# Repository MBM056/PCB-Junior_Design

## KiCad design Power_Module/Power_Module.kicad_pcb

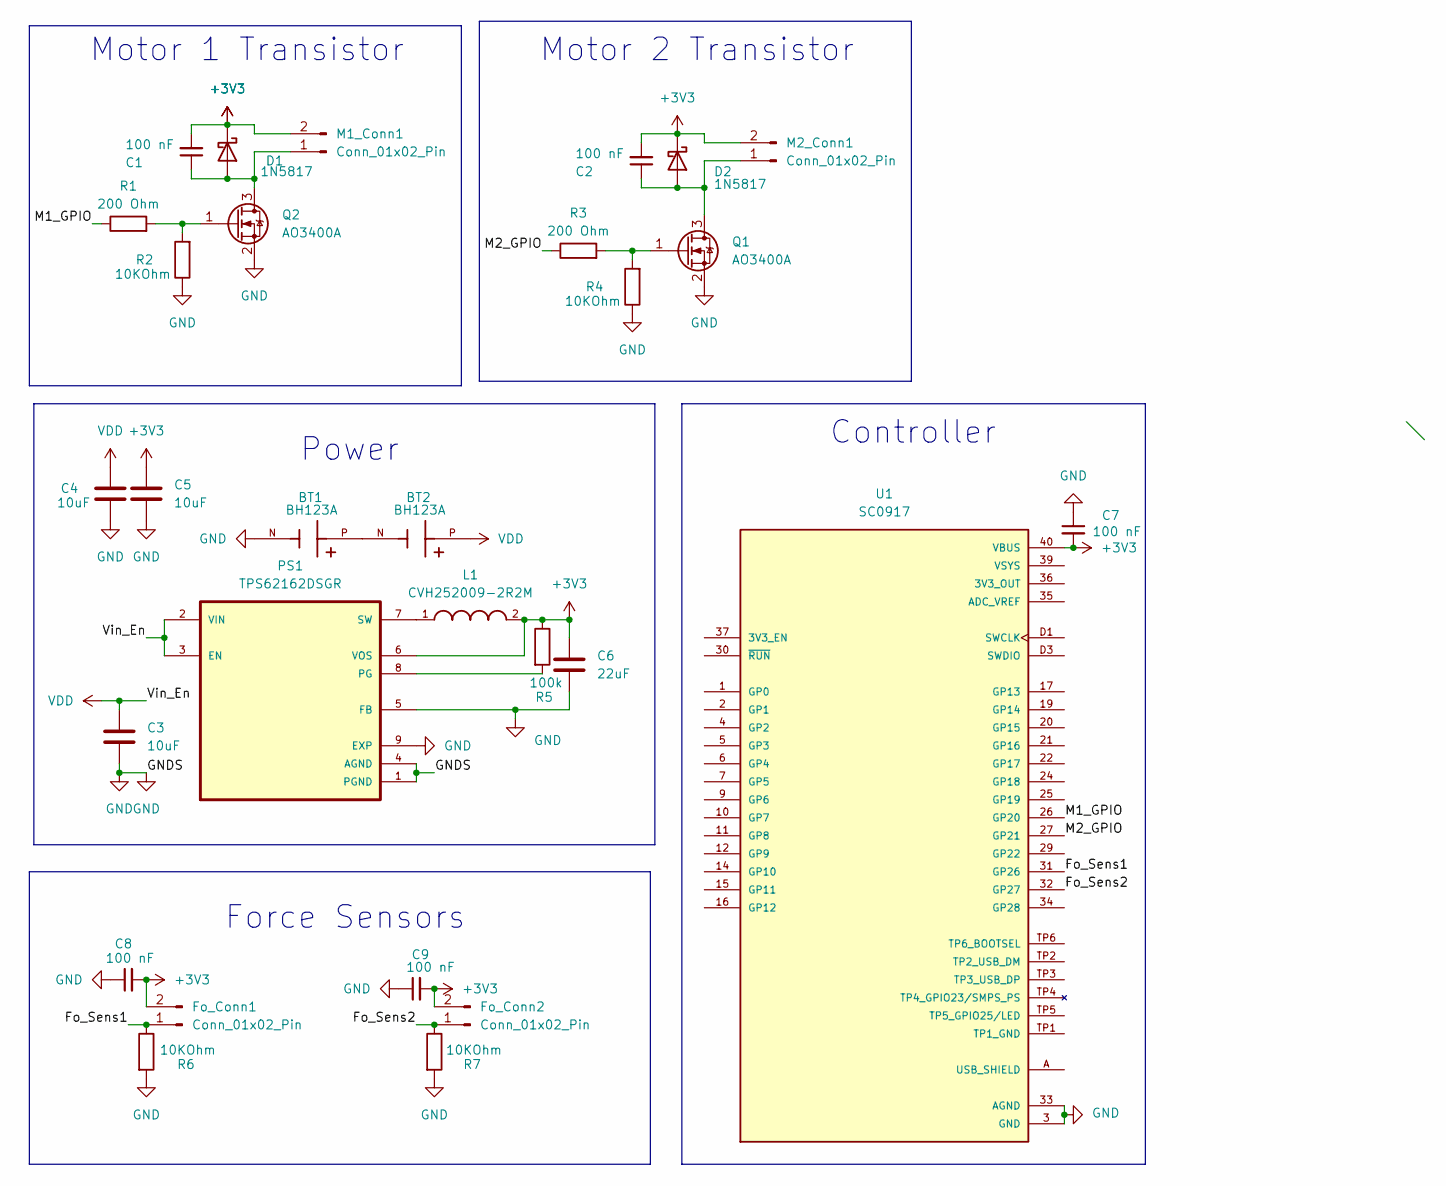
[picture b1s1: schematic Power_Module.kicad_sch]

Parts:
BT1, BT2: BH123A; BAT_BH123A; PARTREV E
C1, C2, C7, C8, C9: 100 nF; C_Disc_D3.0mm_W2.0mm_P2.50mm
C3, C4, C5: 10uF; C_Radial_D5.0mm_H5.0mm_P2.00mm
C6: 22uF; C_Radial_D5.0mm_H5.0mm_P2.00mm
D1, D2: 1N5817; D_A-405_P7.62mm_Horizontal
Fo_Conn1, Fo_Conn2: Conn_01x02_Pin; PinHeader_1x02_P2.54mm_Vertical
L1: CVH252009-2R2M; INDC2520X100N
M1_Conn1, M2_Conn1: Conn_01x02_Pin; PinHeader_1x02_P2.54mm_Vertical
PS1: TPS62162DSGR; SON50P200X200X80-9N; PARTREV E; DigiKey_Part_Number 296-43671-1-ND
Q1, Q2: AO3400A; SOT-23_Handsoldering
R1, R3: 200 Ohm; R_Axial_DIN0204_L3.6mm_D1.6mm_P5.08mm_Horizontal
R2, R4, R6, R7: 10KOhm; R_Axial_DIN0204_L3.6mm_D1.6mm_P5.08mm_Horizontal
R5: 100k; R_Axial_DIN0204_L3.6mm_D1.6mm_P5.08mm_Horizontal
U1: SC0917; MODULE_SC0917; PARTREV 1.9

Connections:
+3V3: C1.2, C2.2, C5.2, C6.1, C7.2, C8.2, C9.2, D1.1 (K), D2.1 (K), Fo_Conn1.2, Fo_Conn2.2, L1.2, M1_Conn1.2, M2_Conn1.2, PS1.6 (VOS), R5.1, U1.40 (VBUS)
/Fo_Sens1: Fo_Conn1.1, R6.1, U1.31 (GP26)
/Fo_Sens2: Fo_Conn2.1, R7.1, U1.32 (GP27)
/M1_GPIO: R1.1, U1.26 (GP20)
/M2_GPIO: R3.1, U1.27 (GP21)
GND: BT1.N, C3.2, C4.2, C5.1, C6.2, C7.1, C8.1, C9.1, PS1.1 (PGND), PS1.4 (AGND), PS1.5 (FB), PS1.9 (EXP), Q1.2 (S), Q2.2 (S), R2.1, R4.1, R6.2, R7.2, U1.3 (GND), U1.8 (GND), U1.13 (GND), U1.18 (GND), U1.23 (GND), U1.28 (GND), U1.33 (AGND), U1.38 (GND), U1.D2 (GND)
unnamed: BT1.P, BT2.N
unnamed: C1.1, D1.2 (A), M1_Conn1.1, Q2.3 (D)
unnamed: C2.1, D2.2 (A), M2_Conn1.1, Q1.3 (D)
unnamed: PS1.8 (PG), R5.2
unnamed: L1.1, PS1.7 (SW)
unnamed: Q1.1 (G), R3.2, R4.2
unnamed: Q2.1 (G), R1.2, R2.2
USB_SHIELD: U1.A (USB_SHIELD), U1.B (USB_SHIELD), U1.C (USB_SHIELD), U1.D (USB_SHIELD)
VDD: BT2.P, C3.1, C4.1, PS1.2 (VIN), PS1.3 (EN)

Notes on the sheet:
Motor 1 Transistor
Controller
Power
Motor 2 Transistor
Force Sensors

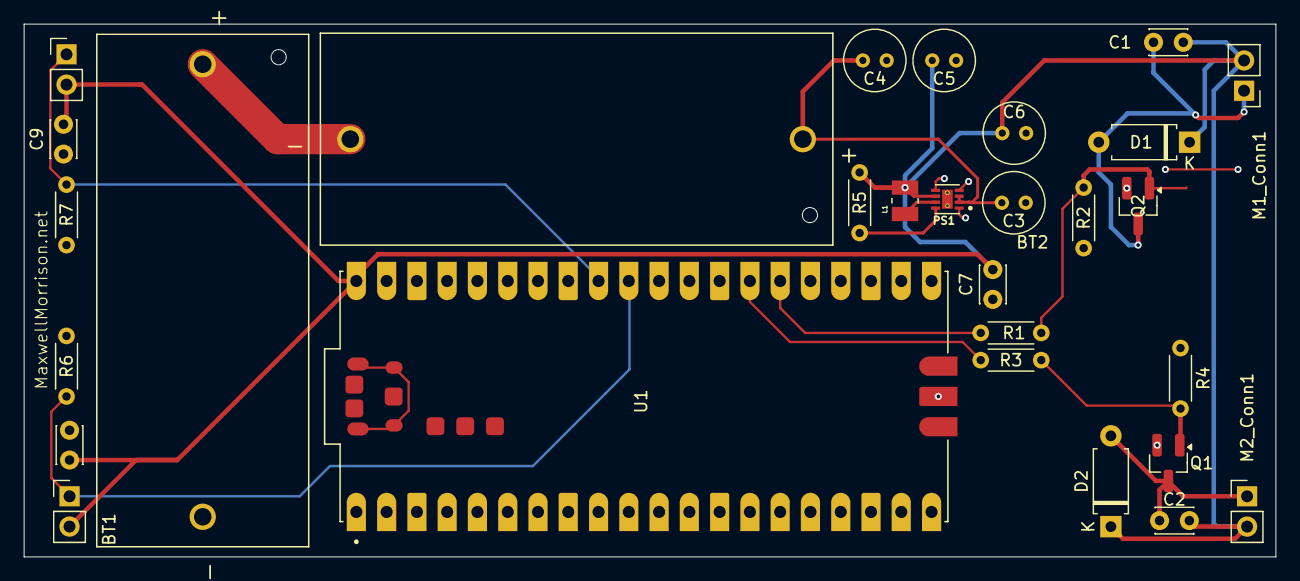
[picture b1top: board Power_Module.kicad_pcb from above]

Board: 2 copper layers, 105.0 x 44.7 mm, 29 parts (0 on the bottom side), 15 nets.

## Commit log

2026-03-12 ititial commit
2026-03-14 This is the changes for the motor controllers and the power module
2026-03-15 Board Final for check by Lum or Martin
